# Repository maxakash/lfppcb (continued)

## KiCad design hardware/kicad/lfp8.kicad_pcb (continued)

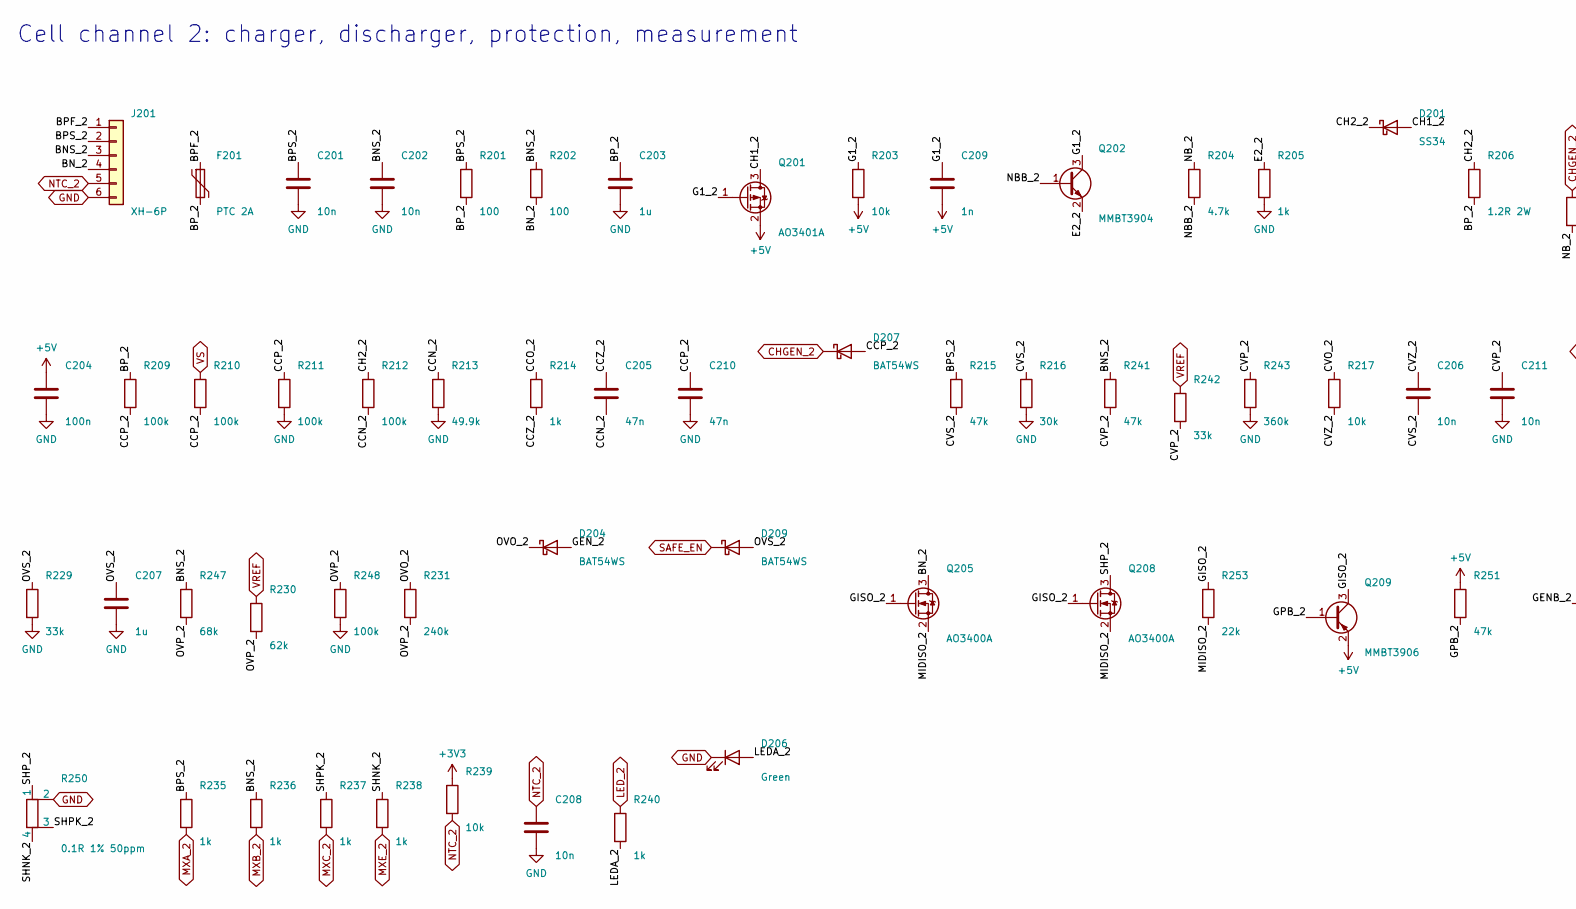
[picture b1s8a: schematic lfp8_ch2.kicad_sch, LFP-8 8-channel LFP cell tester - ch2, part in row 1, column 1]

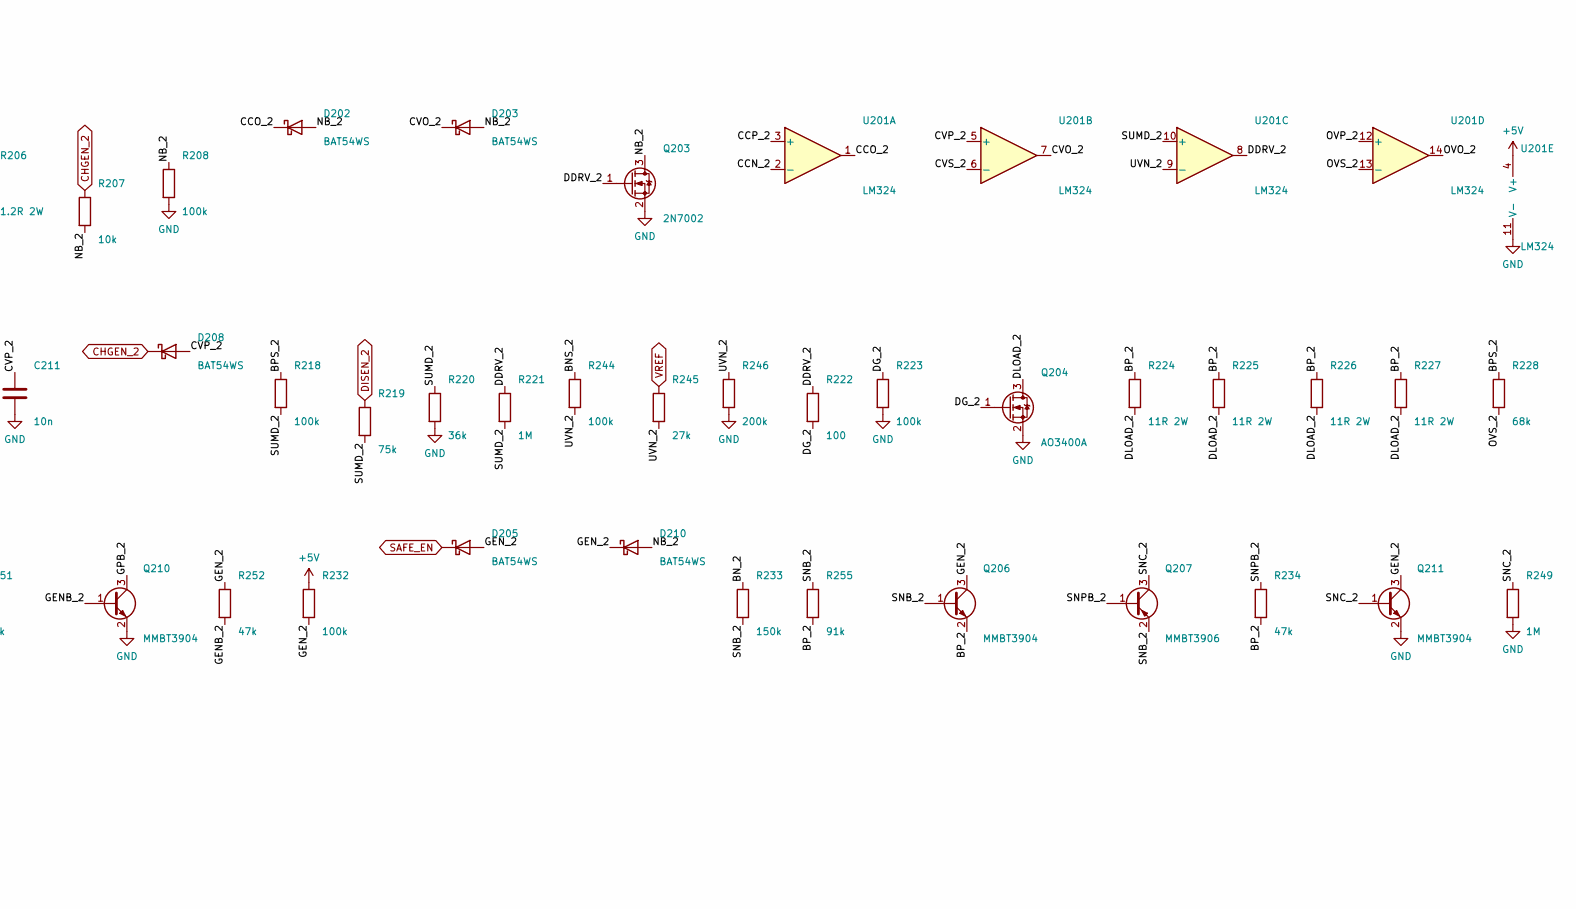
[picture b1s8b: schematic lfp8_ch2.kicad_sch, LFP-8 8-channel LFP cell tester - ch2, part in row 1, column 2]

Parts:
C201, C202, C206, C208, C211: 10n; C_0603_1608Metric; LCSC C57112
C203, C207: 1u; C_0603_1608Metric; LCSC C15849
C204: 100n; C_0603_1608Metric; LCSC C14663
C205, C210: 47n; C_0603_1608Metric; LCSC C1622
C209: 1n; C_0603_1608Metric; LCSC C1588
D201: SS34; D_SMA; MPN SS34; LCSC C8678
D202, D203, D204, D205, D207, D208, D209, D210: BAT54WS; D_SOD-323; MPN BAT54WS; LCSC C7502694
D206: Green; LED_0805_2012Metric; MPN 0805 green; LCSC C2297
F201: PTC 2A; Fuse_1812_4532Metric; MPN 1812L200/30GR; LCSC C18198342
J201: XH-6P; JST_XH_B6B-XH-A_1x06_P2.50mm_Vertical; MPN JST B6B-XH-A (or clone); JLC Hand
Q201: AO3401A; SOT-23; MPN AO3401A; LCSC C15127
Q202, Q206, Q210, Q211: MMBT3904; SOT-23; MPN MMBT3904; LCSC C20526
Q203: 2N7002; SOT-23; MPN 2N7002; LCSC C8545
Q204, Q205, Q208: AO3400A; SOT-23; MPN AO3400A; LCSC C20917
Q207, Q209: MMBT3906; SOT-23; MPN MMBT3906; LCSC C7420354
R201, R202, R222: 100; R_0603_1608Metric; LCSC C22775
R203, R207, R217, R239: 10k; R_0603_1608Metric; LCSC C25804
R204: 4.7k; R_0603_1608Metric; LCSC C23162
R205, R214, R235, R236, R237, R238, R240: 1k; R_0603_1608Metric; LCSC C21190
R206: 1.2R 2W; R_2512_6332Metric; MPN FRP2512F1R20TS; LCSC C7468247
R208, R209, R210, R211, R212, R218, R223, R232, R244, R248: 100k; R_0603_1608Metric; LCSC C25803
R213: 49.9k; R_0603_1608Metric; LCSC C23184
R215, R234, R241, R251, R252: 47k; R_0603_1608Metric; LCSC C25819
R216: 30k; R_0603_1608Metric; LCSC C22984
R219: 75k; R_0603_1608Metric; LCSC C23242
R220: 36k; R_0603_1608Metric; LCSC C23147
R221, R249: 1M; R_0603_1608Metric; LCSC C22935
R224, R225, R226, R227: 11R 2W; R_2512_6332Metric; MPN FRP2512F11R0TS; LCSC C7468192
R228, R247: 68k; R_0603_1608Metric; LCSC C23231
R229, R242: 33k; R_0603_1608Metric; LCSC C4216
R230: 62k; R_0603_1608Metric; LCSC C23221
R231: 240k; R_0603_1608Metric; LCSC C4197
R233: 150k; R_0603_1608Metric; LCSC C22807
R243: 360k; R_0603_1608Metric; LCSC C23146
R245: 27k; R_0603_1608Metric; LCSC C22967
R246: 200k; R_0603_1608Metric; LCSC C25811
R250: 0.1R 1% 50ppm; R_2512_Kelvin; MPN FRM252WFR100TN; LCSC C7420048
R253: 22k; R_0603_1608Metric; LCSC C31850
R255: 91k; R_0603_1608Metric; LCSC C23265
U201: LM324; SOIC-14_3.9x8.7mm_P1.27mm; MPN LM324DT; LCSC C71035

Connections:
+3V3: R239.1; also elsewhere on the board
+5V: C204.1, C209.2, Q201.2 (S), Q209.2 (E), R203.2, R232.1, R251.1, U201.4 (V+); also elsewhere on the board
/ch2/BNS_2: C202.1, J201.3, R202.1, R236.1, R241.1, R244.1, R247.1
/ch2/BN_2: J201.4, Q205.3 (D), R202.2, R233.1
/ch2/BPF_2: F201.1, J201.1
/ch2/BPS_2: C201.1, J201.2, R201.1, R215.1, R218.1, R228.1, R235.1
/ch2/BP_2: C203.1, F201.2, Q206.2 (E), R201.2, R206.2, R209.1, R224.1, R225.1, R226.1, R227.1, R234.2, R255.2
/ch2/CCN_2: C205.2, R212.2, R213.1, U201.2 (-)
/ch2/CCO_2: D202.1 (K), R214.1, U201.1
/ch2/CCP_2: C210.1, D207.2 (A), R209.2, R210.2, R211.1, U201.3 (+)
/ch2/CCZ_2: C205.1, R214.2
/ch2/CH1_2: D201.2 (A), Q201.3 (D)
/ch2/CH2_2: D201.1 (K), R206.1, R212.1
/ch2/CVO_2: D203.1 (K), R217.1, U201.7
/ch2/CVP_2: C211.1, D208.2 (A), R241.2, R242.2, R243.1, U201.5 (+)
/ch2/CVS_2: C206.2, R215.2, R216.1, U201.6 (-)
/ch2/CVZ_2: C206.1, R217.2
/ch2/DDRV_2: Q203.1 (G), R221.1, R222.1, U201.8
/ch2/DG_2: Q204.1 (G), R222.2, R223.1
/ch2/DLOAD_2: Q204.3 (D), R224.2, R225.2, R226.2, R227.2
/ch2/E2_2: Q202.2 (E), R205.1
/ch2/G1_2: C209.1, Q201.1 (G), Q202.3 (C), R203.1
/ch2/GENB_2: Q210.1 (B), R252.2
/ch2/GEN_2: D204.2 (A), D205.2 (A), D210.1 (K), Q206.3 (C), Q211.3 (C), R232.2, R252.1
/ch2/GISO_2: Q205.1 (G), Q208.1 (G), Q209.3 (C), R253.1
/ch2/GPB_2: Q209.1 (B), Q210.3 (C), R251.2
/ch2/LEDA_2: D206.2 (A), R240.2
/ch2/MIDISO_2: Q205.2 (S), Q208.2 (S), R253.2
/ch2/NBB_2: Q202.1 (B), R204.2
/ch2/NB_2: D202.2 (A), D203.2 (A), D210.2 (A), Q203.3 (D), R204.1, R207.2, R208.1
/ch2/OVO_2: D204.1 (K), R231.1, U201.14
/ch2/OVP_2: R230.2, R231.2, R247.2, R248.1, U201.12 (+)
/ch2/OVS_2: C207.1, D209.2 (A), R228.2, R229.1, U201.13 (-)
/ch2/SHNK_2: R238.1, R250.4
/ch2/SHPK_2: R237.1, R250.3
/ch2/SHP_2: Q208.3 (D), R250.1
/ch2/SNB_2: Q206.1 (B), Q207.2 (E), R233.2, R255.1
/ch2/SNC_2: Q207.3 (C), Q211.1 (B), R249.1
/ch2/SNPB_2: Q207.1 (B), R234.1
/ch2/SUMD_2: R218.2, R219.2, R220.1, R221.2, U201.10 (+)
/ch2/UVN_2: R244.2, R245.2, R246.1, U201.9 (-)
CHGEN_2: D207.1 (K), D208.1 (K), R207.1; also elsewhere on the board
DISEN_2: R219.1; also elsewhere on the board
GND: C201.2, C202.2, C203.2, C204.2, C207.2, C208.2, C210.2, C211.2, D206.1 (K), J201.6, Q203.2 (S), Q204.2 (S), Q210.2 (E), Q211.2 (E), R205.2, R208.2, R211.2, R213.2, R216.2, R220.2, R223.2, R229.2, R243.2, R246.2, R248.2, R249.2, R250.2, U201.11 (V-); also elsewhere on the board
LED_2: R240.1; also elsewhere on the board
MXA_2: R235.2; also elsewhere on the board
MXB_2: R236.2; also elsewhere on the board
MXC_2: R237.2; also elsewhere on the board
MXE_2: R238.2; also elsewhere on the board
NTC_2: C208.1, J201.5, R239.2; also elsewhere on the board
SAFE_EN: D205.1 (K), D209.1 (K); also elsewhere on the board
VREF: R230.1, R242.1, R245.1; also elsewhere on the board
VS: R210.1; also elsewhere on the board

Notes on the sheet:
Cell channel 2: charger, discharger, protection, measurement

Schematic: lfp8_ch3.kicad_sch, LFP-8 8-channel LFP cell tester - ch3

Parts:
C301, C302, C306, C308, C311: 10n; C_0603_1608Metric; LCSC C57112
C303, C307: 1u; C_0603_1608Metric; LCSC C15849
C304: 100n; C_0603_1608Metric; LCSC C14663
C305, C310: 47n; C_0603_1608Metric; LCSC C1622
C309: 1n; C_0603_1608Metric; LCSC C1588
D301: SS34; D_SMA; MPN SS34; LCSC C8678
D302, D303, D304, D305, D307, D308, D309, D310: BAT54WS; D_SOD-323; MPN BAT54WS; LCSC C7502694
D306: Green; LED_0805_2012Metric; MPN 0805 green; LCSC C2297
F301: PTC 2A; Fuse_1812_4532Metric; MPN 1812L200/30GR; LCSC C18198342
J301: XH-6P; JST_XH_B6B-XH-A_1x06_P2.50mm_Vertical; MPN JST B6B-XH-A (or clone); JLC Hand
Q301: AO3401A; SOT-23; MPN AO3401A; LCSC C15127
Q302, Q306, Q310, Q311: MMBT3904; SOT-23; MPN MMBT3904; LCSC C20526
Q303: 2N7002; SOT-23; MPN 2N7002; LCSC C8545
Q304, Q305, Q308: AO3400A; SOT-23; MPN AO3400A; LCSC C20917
Q307, Q309: MMBT3906; SOT-23; MPN MMBT3906; LCSC C7420354
R301, R302, R322: 100; R_0603_1608Metric; LCSC C22775
R303, R307, R317, R339: 10k; R_0603_1608Metric; LCSC C25804
R304: 4.7k; R_0603_1608Metric; LCSC C23162
R305, R314, R335, R336, R337, R338, R340: 1k; R_0603_1608Metric; LCSC C21190
R306: 1.2R 2W; R_2512_6332Metric; MPN FRP2512F1R20TS; LCSC C7468247
R308, R309, R310, R311, R312, R318, R323, R332, R344, R348: 100k; R_0603_1608Metric; LCSC C25803
R313: 49.9k; R_0603_1608Metric; LCSC C23184
R315, R334, R341, R351, R352: 47k; R_0603_1608Metric; LCSC C25819
R316: 30k; R_0603_1608Metric; LCSC C22984
R319: 75k; R_0603_1608Metric; LCSC C23242
R320: 36k; R_0603_1608Metric; LCSC C23147
R321, R349: 1M; R_0603_1608Metric; LCSC C22935
R324, R325, R326, R327: 11R 2W; R_2512_6332Metric; MPN FRP2512F11R0TS; LCSC C7468192
R328, R347: 68k; R_0603_1608Metric; LCSC C23231
R329, R342: 33k; R_0603_1608Metric; LCSC C4216
R330: 62k; R_0603_1608Metric; LCSC C23221
R331: 240k; R_0603_1608Metric; LCSC C4197
R333: 150k; R_0603_1608Metric; LCSC C22807
R343: 360k; R_0603_1608Metric; LCSC C23146
R345: 27k; R_0603_1608Metric; LCSC C22967
R346: 200k; R_0603_1608Metric; LCSC C25811
R350: 0.1R 1% 50ppm; R_2512_Kelvin; MPN FRM252WFR100TN; LCSC C7420048
R353: 22k; R_0603_1608Metric; LCSC C31850
R355: 91k; R_0603_1608Metric; LCSC C23265
U301: LM324; SOIC-14_3.9x8.7mm_P1.27mm; MPN LM324DT; LCSC C71035

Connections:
+3V3: R339.1; also elsewhere on the board
+5V: C304.1, C309.2, Q301.2 (S), Q309.2 (E), R303.2, R332.1, R351.1, U301.4 (V+); also elsewhere on the board
/ch3/BNS_3: C302.1, J301.3, R302.1, R336.1, R341.1, R344.1, R347.1
/ch3/BN_3: J301.4, Q305.3 (D), R302.2, R333.1
/ch3/BPF_3: F301.1, J301.1
/ch3/BPS_3: C301.1, J301.2, R301.1, R315.1, R318.1, R328.1, R335.1
/ch3/BP_3: C303.1, F301.2, Q306.2 (E), R301.2, R306.2, R309.1, R324.1, R325.1, R326.1, R327.1, R334.2, R355.2
/ch3/CCN_3: C305.2, R312.2, R313.1, U301.2 (-)
/ch3/CCO_3: D302.1 (K), R314.1, U301.1
/ch3/CCP_3: C310.1, D307.2 (A), R309.2, R310.2, R311.1, U301.3 (+)
/ch3/CCZ_3: C305.1, R314.2
/ch3/CH1_3: D301.2 (A), Q301.3 (D)
/ch3/CH2_3: D301.1 (K), R306.1, R312.1
/ch3/CVO_3: D303.1 (K), R317.1, U301.7
/ch3/CVP_3: C311.1, D308.2 (A), R341.2, R342.2, R343.1, U301.5 (+)
/ch3/CVS_3: C306.2, R315.2, R316.1, U301.6 (-)
/ch3/CVZ_3: C306.1, R317.2
/ch3/DDRV_3: Q303.1 (G), R321.1, R322.1, U301.8
/ch3/DG_3: Q304.1 (G), R322.2, R323.1
/ch3/DLOAD_3: Q304.3 (D), R324.2, R325.2, R326.2, R327.2
/ch3/E2_3: Q302.2 (E), R305.1
/ch3/G1_3: C309.1, Q301.1 (G), Q302.3 (C), R303.1
/ch3/GENB_3: Q310.1 (B), R352.2
/ch3/GEN_3: D304.2 (A), D305.2 (A), D310.1 (K), Q306.3 (C), Q311.3 (C), R332.2, R352.1
/ch3/GISO_3: Q305.1 (G), Q308.1 (G), Q309.3 (C), R353.1
/ch3/GPB_3: Q309.1 (B), Q310.3 (C), R351.2
/ch3/LEDA_3: D306.2 (A), R340.2
/ch3/MIDISO_3: Q305.2 (S), Q308.2 (S), R353.2
/ch3/NBB_3: Q302.1 (B), R304.2
/ch3/NB_3: D302.2 (A), D303.2 (A), D310.2 (A), Q303.3 (D), R304.1, R307.2, R308.1
/ch3/OVO_3: D304.1 (K), R331.1, U301.14
/ch3/OVP_3: R330.2, R331.2, R347.2, R348.1, U301.12 (+)
/ch3/OVS_3: C307.1, D309.2 (A), R328.2, R329.1, U301.13 (-)
/ch3/SHNK_3: R338.1, R350.4
/ch3/SHPK_3: R337.1, R350.3
/ch3/SHP_3: Q308.3 (D), R350.1
/ch3/SNB_3: Q306.1 (B), Q307.2 (E), R333.2, R355.1
/ch3/SNC_3: Q307.3 (C), Q311.1 (B), R349.1
/ch3/SNPB_3: Q307.1 (B), R334.1
/ch3/SUMD_3: R318.2, R319.2, R320.1, R321.2, U301.10 (+)
/ch3/UVN_3: R344.2, R345.2, R346.1, U301.9 (-)
CHGEN_3: D307.1 (K), D308.1 (K), R307.1; also elsewhere on the board
DISEN_3: R319.1; also elsewhere on the board
GND: C301.2, C302.2, C303.2, C304.2, C307.2, C308.2, C310.2, C311.2, D306.1 (K), J301.6, Q303.2 (S), Q304.2 (S), Q310.2 (E), Q311.2 (E), R305.2, R308.2, R311.2, R313.2, R316.2, R320.2, R323.2, R329.2, R343.2, R346.2, R348.2, R349.2, R350.2, U301.11 (V-); also elsewhere on the board
LED_3: R340.1; also elsewhere on the board
MXA_3: R335.2; also elsewhere on the board
MXB_3: R336.2; also elsewhere on the board
MXC_3: R337.2; also elsewhere on the board
MXE_3: R338.2; also elsewhere on the board
NTC_3: C308.1, J301.5, R339.2; also elsewhere on the board
SAFE_EN: D305.1 (K), D309.1 (K); also elsewhere on the board
VREF: R330.1, R342.1, R345.1; also elsewhere on the board
VS: R310.1; also elsewhere on the board

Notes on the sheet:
Cell channel 3: charger, discharger, protection, measurement

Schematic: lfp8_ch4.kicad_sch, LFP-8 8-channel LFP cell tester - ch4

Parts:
C401, C402, C406, C408, C411: 10n; C_0603_1608Metric; LCSC C57112
C403, C407: 1u; C_0603_1608Metric; LCSC C15849
C404: 100n; C_0603_1608Metric; LCSC C14663
C405, C410: 47n; C_0603_1608Metric; LCSC C1622
C409: 1n; C_0603_1608Metric; LCSC C1588
D401: SS34; D_SMA; MPN SS34; LCSC C8678
D402, D403, D404, D405, D407, D408, D409, D410: BAT54WS; D_SOD-323; MPN BAT54WS; LCSC C7502694
D406: Green; LED_0805_2012Metric; MPN 0805 green; LCSC C2297
F401: PTC 2A; Fuse_1812_4532Metric; MPN 1812L200/30GR; LCSC C18198342
J401: XH-6P; JST_XH_B6B-XH-A_1x06_P2.50mm_Vertical; MPN JST B6B-XH-A (or clone); JLC Hand
Q401: AO3401A; SOT-23; MPN AO3401A; LCSC C15127
Q402, Q406, Q410, Q411: MMBT3904; SOT-23; MPN MMBT3904; LCSC C20526
Q403: 2N7002; SOT-23; MPN 2N7002; LCSC C8545
Q404, Q405, Q408: AO3400A; SOT-23; MPN AO3400A; LCSC C20917
Q407, Q409: MMBT3906; SOT-23; MPN MMBT3906; LCSC C7420354
R401, R402, R422: 100; R_0603_1608Metric; LCSC C22775
R403, R407, R417, R439: 10k; R_0603_1608Metric; LCSC C25804
R404: 4.7k; R_0603_1608Metric; LCSC C23162
R405, R414, R435, R436, R437, R438, R440: 1k; R_0603_1608Metric; LCSC C21190
R406: 1.2R 2W; R_2512_6332Metric; MPN FRP2512F1R20TS; LCSC C7468247
R408, R409, R410, R411, R412, R418, R423, R432, R444, R448: 100k; R_0603_1608Metric; LCSC C25803
R413: 49.9k; R_0603_1608Metric; LCSC C23184
R415, R434, R441, R451, R452: 47k; R_0603_1608Metric; LCSC C25819
R416: 30k; R_0603_1608Metric; LCSC C22984
R419: 75k; R_0603_1608Metric; LCSC C23242
R420: 36k; R_0603_1608Metric; LCSC C23147
R421, R449: 1M; R_0603_1608Metric; LCSC C22935
R424, R425, R426, R427: 11R 2W; R_2512_6332Metric; MPN FRP2512F11R0TS; LCSC C7468192
R428, R447: 68k; R_0603_1608Metric; LCSC C23231
R429, R442: 33k; R_0603_1608Metric; LCSC C4216
R430: 62k; R_0603_1608Metric; LCSC C23221
R431: 240k; R_0603_1608Metric; LCSC C4197
R433: 150k; R_0603_1608Metric; LCSC C22807
R443: 360k; R_0603_1608Metric; LCSC C23146
R445: 27k; R_0603_1608Metric; LCSC C22967
R446: 200k; R_0603_1608Metric; LCSC C25811
R450: 0.1R 1% 50ppm; R_2512_Kelvin; MPN FRM252WFR100TN; LCSC C7420048
R453: 22k; R_0603_1608Metric; LCSC C31850
R455: 91k; R_0603_1608Metric; LCSC C23265
U401: LM324; SOIC-14_3.9x8.7mm_P1.27mm; MPN LM324DT; LCSC C71035

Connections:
+3V3: R439.1; also elsewhere on the board
+5V: C404.1, C409.2, Q401.2 (S), Q409.2 (E), R403.2, R432.1, R451.1, U401.4 (V+); also elsewhere on the board
/ch4/BNS_4: C402.1, J401.3, R402.1, R436.1, R441.1, R444.1, R447.1
/ch4/BN_4: J401.4, Q405.3 (D), R402.2, R433.1
/ch4/BPF_4: F401.1, J401.1
/ch4/BPS_4: C401.1, J401.2, R401.1, R415.1, R418.1, R428.1, R435.1
/ch4/BP_4: C403.1, F401.2, Q406.2 (E), R401.2, R406.2, R409.1, R424.1, R425.1, R426.1, R427.1, R434.2, R455.2
/ch4/CCN_4: C405.2, R412.2, R413.1, U401.2 (-)
/ch4/CCO_4: D402.1 (K), R414.1, U401.1
/ch4/CCP_4: C410.1, D407.2 (A), R409.2, R410.2, R411.1, U401.3 (+)
/ch4/CCZ_4: C405.1, R414.2
/ch4/CH1_4: D401.2 (A), Q401.3 (D)
/ch4/CH2_4: D401.1 (K), R406.1, R412.1
/ch4/CVO_4: D403.1 (K), R417.1, U401.7
/ch4/CVP_4: C411.1, D408.2 (A), R441.2, R442.2, R443.1, U401.5 (+)
/ch4/CVS_4: C406.2, R415.2, R416.1, U401.6 (-)
/ch4/CVZ_4: C406.1, R417.2
/ch4/DDRV_4: Q403.1 (G), R421.1, R422.1, U401.8
/ch4/DG_4: Q404.1 (G), R422.2, R423.1
/ch4/DLOAD_4: Q404.3 (D), R424.2, R425.2, R426.2, R427.2
/ch4/E2_4: Q402.2 (E), R405.1
/ch4/G1_4: C409.1, Q401.1 (G), Q402.3 (C), R403.1
/ch4/GENB_4: Q410.1 (B), R452.2
/ch4/GEN_4: D404.2 (A), D405.2 (A), D410.1 (K), Q406.3 (C), Q411.3 (C), R432.2, R452.1
/ch4/GISO_4: Q405.1 (G), Q408.1 (G), Q409.3 (C), R453.1
/ch4/GPB_4: Q409.1 (B), Q410.3 (C), R451.2
/ch4/LEDA_4: D406.2 (A), R440.2
/ch4/MIDISO_4: Q405.2 (S), Q408.2 (S), R453.2
/ch4/NBB_4: Q402.1 (B), R404.2
/ch4/NB_4: D402.2 (A), D403.2 (A), D410.2 (A), Q403.3 (D), R404.1, R407.2, R408.1
/ch4/OVO_4: D404.1 (K), R431.1, U401.14
/ch4/OVP_4: R430.2, R431.2, R447.2, R448.1, U401.12 (+)
/ch4/OVS_4: C407.1, D409.2 (A), R428.2, R429.1, U401.13 (-)
/ch4/SHNK_4: R438.1, R450.4
/ch4/SHPK_4: R437.1, R450.3
/ch4/SHP_4: Q408.3 (D), R450.1
/ch4/SNB_4: Q406.1 (B), Q407.2 (E), R433.2, R455.1
/ch4/SNC_4: Q407.3 (C), Q411.1 (B), R449.1
/ch4/SNPB_4: Q407.1 (B), R434.1
/ch4/SUMD_4: R418.2, R419.2, R420.1, R421.2, U401.10 (+)
/ch4/UVN_4: R444.2, R445.2, R446.1, U401.9 (-)
CHGEN_4: D407.1 (K), D408.1 (K), R407.1; also elsewhere on the board
DISEN_4: R419.1; also elsewhere on the board
GND: C401.2, C402.2, C403.2, C404.2, C407.2, C408.2, C410.2, C411.2, D406.1 (K), J401.6, Q403.2 (S), Q404.2 (S), Q410.2 (E), Q411.2 (E), R405.2, R408.2, R411.2, R413.2, R416.2, R420.2, R423.2, R429.2, R443.2, R446.2, R448.2, R449.2, R450.2, U401.11 (V-); also elsewhere on the board
LED_4: R440.1; also elsewhere on the board
MXA_4: R435.2; also elsewhere on the board
MXB_4: R436.2; also elsewhere on the board
MXC_4: R437.2; also elsewhere on the board
MXE_4: R438.2; also elsewhere on the board
NTC_4: C408.1, J401.5, R439.2; also elsewhere on the board
SAFE_EN: D405.1 (K), D409.1 (K); also elsewhere on the board
VREF: R430.1, R442.1, R445.1; also elsewhere on the board
VS: R410.1; also elsewhere on the board

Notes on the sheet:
Cell channel 4: charger, discharger, protection, measurement

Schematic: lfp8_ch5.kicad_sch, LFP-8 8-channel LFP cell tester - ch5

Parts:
C501, C502, C506, C508, C511: 10n; C_0603_1608Metric; LCSC C57112
C503, C507: 1u; C_0603_1608Metric; LCSC C15849
C504: 100n; C_0603_1608Metric; LCSC C14663
C505, C510: 47n; C_0603_1608Metric; LCSC C1622
C509: 1n; C_0603_1608Metric; LCSC C1588
D501: SS34; D_SMA; MPN SS34; LCSC C8678
D502, D503, D504, D505, D507, D508, D509, D510: BAT54WS; D_SOD-323; MPN BAT54WS; LCSC C7502694
D506: Green; LED_0805_2012Metric; MPN 0805 green; LCSC C2297
F501: PTC 2A; Fuse_1812_4532Metric; MPN 1812L200/30GR; LCSC C18198342
J501: XH-6P; JST_XH_B6B-XH-A_1x06_P2.50mm_Vertical; MPN JST B6B-XH-A (or clone); JLC Hand
Q501: AO3401A; SOT-23; MPN AO3401A; LCSC C15127
Q502, Q506, Q510, Q511: MMBT3904; SOT-23; MPN MMBT3904; LCSC C20526
Q503: 2N7002; SOT-23; MPN 2N7002; LCSC C8545
Q504, Q505, Q508: AO3400A; SOT-23; MPN AO3400A; LCSC C20917
Q507, Q509: MMBT3906; SOT-23; MPN MMBT3906; LCSC C7420354
R501, R502, R522: 100; R_0603_1608Metric; LCSC C22775
R503, R507, R517, R539: 10k; R_0603_1608Metric; LCSC C25804
R504: 4.7k; R_0603_1608Metric; LCSC C23162
R505, R514, R535, R536, R537, R538, R540: 1k; R_0603_1608Metric; LCSC C21190
R506: 1.2R 2W; R_2512_6332Metric; MPN FRP2512F1R20TS; LCSC C7468247
R508, R509, R510, R511, R512, R518, R523, R532, R544, R548: 100k; R_0603_1608Metric; LCSC C25803
R513: 49.9k; R_0603_1608Metric; LCSC C23184
R515, R534, R541, R551, R552: 47k; R_0603_1608Metric; LCSC C25819
R516: 30k; R_0603_1608Metric; LCSC C22984
R519: 75k; R_0603_1608Metric; LCSC C23242
R520: 36k; R_0603_1608Metric; LCSC C23147
R521, R549: 1M; R_0603_1608Metric; LCSC C22935
R524, R525, R526, R527: 11R 2W; R_2512_6332Metric; MPN FRP2512F11R0TS; LCSC C7468192
R528, R547: 68k; R_0603_1608Metric; LCSC C23231
R529, R542: 33k; R_0603_1608Metric; LCSC C4216
R530: 62k; R_0603_1608Metric; LCSC C23221
R531: 240k; R_0603_1608Metric; LCSC C4197
R533: 150k; R_0603_1608Metric; LCSC C22807
R543: 360k; R_0603_1608Metric; LCSC C23146
R545: 27k; R_0603_1608Metric; LCSC C22967
R546: 200k; R_0603_1608Metric; LCSC C25811
R550: 0.1R 1% 50ppm; R_2512_Kelvin; MPN FRM252WFR100TN; LCSC C7420048
R553: 22k; R_0603_1608Metric; LCSC C31850
R555: 91k; R_0603_1608Metric; LCSC C23265
U501: LM324; SOIC-14_3.9x8.7mm_P1.27mm; MPN LM324DT; LCSC C71035

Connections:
+3V3: R539.1; also elsewhere on the board
+5V: C504.1, C509.2, Q501.2 (S), Q509.2 (E), R503.2, R532.1, R551.1, U501.4 (V+); also elsewhere on the board
/ch5/BNS_5: C502.1, J501.3, R502.1, R536.1, R541.1, R544.1, R547.1
/ch5/BN_5: J501.4, Q505.3 (D), R502.2, R533.1
/ch5/BPF_5: F501.1, J501.1
/ch5/BPS_5: C501.1, J501.2, R501.1, R515.1, R518.1, R528.1, R535.1
/ch5/BP_5: C503.1, F501.2, Q506.2 (E), R501.2, R506.2, R509.1, R524.1, R525.1, R526.1, R527.1, R534.2, R555.2
/ch5/CCN_5: C505.2, R512.2, R513.1, U501.2 (-)
/ch5/CCO_5: D502.1 (K), R514.1, U501.1
/ch5/CCP_5: C510.1, D507.2 (A), R509.2, R510.2, R511.1, U501.3 (+)
/ch5/CCZ_5: C505.1, R514.2
/ch5/CH1_5: D501.2 (A), Q501.3 (D)
/ch5/CH2_5: D501.1 (K), R506.1, R512.1
/ch5/CVO_5: D503.1 (K), R517.1, U501.7
/ch5/CVP_5: C511.1, D508.2 (A), R541.2, R542.2, R543.1, U501.5 (+)
/ch5/CVS_5: C506.2, R515.2, R516.1, U501.6 (-)
/ch5/CVZ_5: C506.1, R517.2
/ch5/DDRV_5: Q503.1 (G), R521.1, R522.1, U501.8
/ch5/DG_5: Q504.1 (G), R522.2, R523.1
/ch5/DLOAD_5: Q504.3 (D), R524.2, R525.2, R526.2, R527.2
/ch5/E2_5: Q502.2 (E), R505.1
/ch5/G1_5: C509.1, Q501.1 (G), Q502.3 (C), R503.1
/ch5/GENB_5: Q510.1 (B), R552.2
/ch5/GEN_5: D504.2 (A), D505.2 (A), D510.1 (K), Q506.3 (C), Q511.3 (C), R532.2, R552.1
/ch5/GISO_5: Q505.1 (G), Q508.1 (G), Q509.3 (C), R553.1
/ch5/GPB_5: Q509.1 (B), Q510.3 (C), R551.2
/ch5/LEDA_5: D506.2 (A), R540.2
/ch5/MIDISO_5: Q505.2 (S), Q508.2 (S), R553.2
/ch5/NBB_5: Q502.1 (B), R504.2
/ch5/NB_5: D502.2 (A), D503.2 (A), D510.2 (A), Q503.3 (D), R504.1, R507.2, R508.1
/ch5/OVO_5: D504.1 (K), R531.1, U501.14
/ch5/OVP_5: R530.2, R531.2, R547.2, R548.1, U501.12 (+)
/ch5/OVS_5: C507.1, D509.2 (A), R528.2, R529.1, U501.13 (-)
/ch5/SHNK_5: R538.1, R550.4
/ch5/SHPK_5: R537.1, R550.3
/ch5/SHP_5: Q508.3 (D), R550.1
/ch5/SNB_5: Q506.1 (B), Q507.2 (E), R533.2, R555.1
/ch5/SNC_5: Q507.3 (C), Q511.1 (B), R549.1
/ch5/SNPB_5: Q507.1 (B), R534.1
/ch5/SUMD_5: R518.2, R519.2, R520.1, R521.2, U501.10 (+)
/ch5/UVN_5: R544.2, R545.2, R546.1, U501.9 (-)
CHGEN_5: D507.1 (K), D508.1 (K), R507.1; also elsewhere on the board
DISEN_5: R519.1; also elsewhere on the board
GND: C501.2, C502.2, C503.2, C504.2, C507.2, C508.2, C510.2, C511.2, D506.1 (K), J501.6, Q503.2 (S), Q504.2 (S), Q510.2 (E), Q511.2 (E), R505.2, R508.2, R511.2, R513.2, R516.2, R520.2, R523.2, R529.2, R543.2, R546.2, R548.2, R549.2, R550.2, U501.11 (V-); also elsewhere on the board
LED_5: R540.1; also elsewhere on the board
MXA_5: R535.2; also elsewhere on the board
MXB_5: R536.2; also elsewhere on the board
MXC_5: R537.2; also elsewhere on the board
MXE_5: R538.2; also elsewhere on the board
NTC_5: C508.1, J501.5, R539.2; also elsewhere on the board
SAFE_EN: D505.1 (K), D509.1 (K); also elsewhere on the board
VREF: R530.1, R542.1, R545.1; also elsewhere on the board
VS: R510.1; also elsewhere on the board

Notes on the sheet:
Cell channel 5: charger, discharger, protection, measurement

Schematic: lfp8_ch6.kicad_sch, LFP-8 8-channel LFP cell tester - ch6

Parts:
C601, C602, C606, C608, C611: 10n; C_0603_1608Metric; LCSC C57112
C603, C607: 1u; C_0603_1608Metric; LCSC C15849
C604: 100n; C_0603_1608Metric; LCSC C14663
C605, C610: 47n; C_0603_1608Metric; LCSC C1622
C609: 1n; C_0603_1608Metric; LCSC C1588
D601: SS34; D_SMA; MPN SS34; LCSC C8678
D602, D603, D604, D605, D607, D608, D609, D610: BAT54WS; D_SOD-323; MPN BAT54WS; LCSC C7502694
D606: Green; LED_0805_2012Metric; MPN 0805 green; LCSC C2297
F601: PTC 2A; Fuse_1812_4532Metric; MPN 1812L200/30GR; LCSC C18198342
J601: XH-6P; JST_XH_B6B-XH-A_1x06_P2.50mm_Vertical; MPN JST B6B-XH-A (or clone); JLC Hand
Q601: AO3401A; SOT-23; MPN AO3401A; LCSC C15127
Q602, Q606, Q610, Q611: MMBT3904; SOT-23; MPN MMBT3904; LCSC C20526
Q603: 2N7002; SOT-23; MPN 2N7002; LCSC C8545
Q604, Q605, Q608: AO3400A; SOT-23; MPN AO3400A; LCSC C20917
Q607, Q609: MMBT3906; SOT-23; MPN MMBT3906; LCSC C7420354
R601, R602, R622: 100; R_0603_1608Metric; LCSC C22775
R603, R607, R617, R639: 10k; R_0603_1608Metric; LCSC C25804
R604: 4.7k; R_0603_1608Metric; LCSC C23162
R605, R614, R635, R636, R637, R638, R640: 1k; R_0603_1608Metric; LCSC C21190
R606: 1.2R 2W; R_2512_6332Metric; MPN FRP2512F1R20TS; LCSC C7468247
R608, R609, R610, R611, R612, R618, R623, R632, R644, R648: 100k; R_0603_1608Metric; LCSC C25803
R613: 49.9k; R_0603_1608Metric; LCSC C23184
R615, R634, R641, R651, R652: 47k; R_0603_1608Metric; LCSC C25819
R616: 30k; R_0603_1608Metric; LCSC C22984
R619: 75k; R_0603_1608Metric; LCSC C23242
R620: 36k; R_0603_1608Metric; LCSC C23147
R621, R649: 1M; R_0603_1608Metric; LCSC C22935
R624, R625, R626, R627: 11R 2W; R_2512_6332Metric; MPN FRP2512F11R0TS; LCSC C7468192
R628, R647: 68k; R_0603_1608Metric; LCSC C23231
R629, R642: 33k; R_0603_1608Metric; LCSC C4216
R630: 62k; R_0603_1608Metric; LCSC C23221
R631: 240k; R_0603_1608Metric; LCSC C4197
R633: 150k; R_0603_1608Metric; LCSC C22807
R643: 360k; R_0603_1608Metric; LCSC C23146
R645: 27k; R_0603_1608Metric; LCSC C22967
R646: 200k; R_0603_1608Metric; LCSC C25811
R650: 0.1R 1% 50ppm; R_2512_Kelvin; MPN FRM252WFR100TN; LCSC C7420048
R653: 22k; R_0603_1608Metric; LCSC C31850
R655: 91k; R_0603_1608Metric; LCSC C23265
U601: LM324; SOIC-14_3.9x8.7mm_P1.27mm; MPN LM324DT; LCSC C71035

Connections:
+3V3: R639.1; also elsewhere on the board
+5V: C604.1, C609.2, Q601.2 (S), Q609.2 (E), R603.2, R632.1, R651.1, U601.4 (V+); also elsewhere on the board
/ch6/BNS_6: C602.1, J601.3, R602.1, R636.1, R641.1, R644.1, R647.1
/ch6/BN_6: J601.4, Q605.3 (D), R602.2, R633.1
/ch6/BPF_6: F601.1, J601.1
/ch6/BPS_6: C601.1, J601.2, R601.1, R615.1, R618.1, R628.1, R635.1
/ch6/BP_6: C603.1, F601.2, Q606.2 (E), R601.2, R606.2, R609.1, R624.1, R625.1, R626.1, R627.1, R634.2, R655.2
/ch6/CCN_6: C605.2, R612.2, R613.1, U601.2 (-)
/ch6/CCO_6: D602.1 (K), R614.1, U601.1
/ch6/CCP_6: C610.1, D607.2 (A), R609.2, R610.2, R611.1, U601.3 (+)
/ch6/CCZ_6: C605.1, R614.2
/ch6/CH1_6: D601.2 (A), Q601.3 (D)
/ch6/CH2_6: D601.1 (K), R606.1, R612.1
/ch6/CVO_6: D603.1 (K), R617.1, U601.7
/ch6/CVP_6: C611.1, D608.2 (A), R641.2, R642.2, R643.1, U601.5 (+)
/ch6/CVS_6: C606.2, R615.2, R616.1, U601.6 (-)
/ch6/CVZ_6: C606.1, R617.2
/ch6/DDRV_6: Q603.1 (G), R621.1, R622.1, U601.8
/ch6/DG_6: Q604.1 (G), R622.2, R623.1
/ch6/DLOAD_6: Q604.3 (D), R624.2, R625.2, R626.2, R627.2
/ch6/E2_6: Q602.2 (E), R605.1
/ch6/G1_6: C609.1, Q601.1 (G), Q602.3 (C), R603.1
/ch6/GENB_6: Q610.1 (B), R652.2
/ch6/GEN_6: D604.2 (A), D605.2 (A), D610.1 (K), Q606.3 (C), Q611.3 (C), R632.2, R652.1
/ch6/GISO_6: Q605.1 (G), Q608.1 (G), Q609.3 (C), R653.1
/ch6/GPB_6: Q609.1 (B), Q610.3 (C), R651.2
/ch6/LEDA_6: D606.2 (A), R640.2
/ch6/MIDISO_6: Q605.2 (S), Q608.2 (S), R653.2
/ch6/NBB_6: Q602.1 (B), R604.2
/ch6/NB_6: D602.2 (A), D603.2 (A), D610.2 (A), Q603.3 (D), R604.1, R607.2, R608.1
/ch6/OVO_6: D604.1 (K), R631.1, U601.14
/ch6/OVP_6: R630.2, R631.2, R647.2, R648.1, U601.12 (+)
/ch6/OVS_6: C607.1, D609.2 (A), R628.2, R629.1, U601.13 (-)
/ch6/SHNK_6: R638.1, R650.4
/ch6/SHPK_6: R637.1, R650.3
/ch6/SHP_6: Q608.3 (D), R650.1
/ch6/SNB_6: Q606.1 (B), Q607.2 (E), R633.2, R655.1
/ch6/SNC_6: Q607.3 (C), Q611.1 (B), R649.1
/ch6/SNPB_6: Q607.1 (B), R634.1
/ch6/SUMD_6: R618.2, R619.2, R620.1, R621.2, U601.10 (+)
/ch6/UVN_6: R644.2, R645.2, R646.1, U601.9 (-)
CHGEN_6: D607.1 (K), D608.1 (K), R607.1; also elsewhere on the board
DISEN_6: R619.1; also elsewhere on the board
GND: C601.2, C602.2, C603.2, C604.2, C607.2, C608.2, C610.2, C611.2, D606.1 (K), J601.6, Q603.2 (S), Q604.2 (S), Q610.2 (E), Q611.2 (E), R605.2, R608.2, R611.2, R613.2, R616.2, R620.2, R623.2, R629.2, R643.2, R646.2, R648.2, R649.2, R650.2, U601.11 (V-); also elsewhere on the board
LED_6: R640.1; also elsewhere on the board
MXA_6: R635.2; also elsewhere on the board
MXB_6: R636.2; also elsewhere on the board
MXC_6: R637.2; also elsewhere on the board
MXE_6: R638.2; also elsewhere on the board
NTC_6: C608.1, J601.5, R639.2; also elsewhere on the board
SAFE_EN: D605.1 (K), D609.1 (K); also elsewhere on the board
VREF: R630.1, R642.1, R645.1; also elsewhere on the board
VS: R610.1; also elsewhere on the board

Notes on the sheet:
Cell channel 6: charger, discharger, protection, measurement

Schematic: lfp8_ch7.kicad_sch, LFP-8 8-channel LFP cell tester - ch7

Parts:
C701, C702, C706, C708, C711: 10n; C_0603_1608Metric; LCSC C57112
C703, C707: 1u; C_0603_1608Metric; LCSC C15849
C704: 100n; C_0603_1608Metric; LCSC C14663
C705, C710: 47n; C_0603_1608Metric; LCSC C1622
C709: 1n; C_0603_1608Metric; LCSC C1588
D701: SS34; D_SMA; MPN SS34; LCSC C8678
D702, D703, D704, D705, D707, D708, D709, D710: BAT54WS; D_SOD-323; MPN BAT54WS; LCSC C7502694
D706: Green; LED_0805_2012Metric; MPN 0805 green; LCSC C2297
F701: PTC 2A; Fuse_1812_4532Metric; MPN 1812L200/30GR; LCSC C18198342
J701: XH-6P; JST_XH_B6B-XH-A_1x06_P2.50mm_Vertical; MPN JST B6B-XH-A (or clone); JLC Hand
Q701: AO3401A; SOT-23; MPN AO3401A; LCSC C15127
Q702, Q706, Q710, Q711: MMBT3904; SOT-23; MPN MMBT3904; LCSC C20526
Q703: 2N7002; SOT-23; MPN 2N7002; LCSC C8545
Q704, Q705, Q708: AO3400A; SOT-23; MPN AO3400A; LCSC C20917
Q707, Q709: MMBT3906; SOT-23; MPN MMBT3906; LCSC C7420354
R701, R702, R722: 100; R_0603_1608Metric; LCSC C22775
R703, R707, R717, R739: 10k; R_0603_1608Metric; LCSC C25804
R704: 4.7k; R_0603_1608Metric; LCSC C23162
R705, R714, R735, R736, R737, R738, R740: 1k; R_0603_1608Metric; LCSC C21190
R706: 1.2R 2W; R_2512_6332Metric; MPN FRP2512F1R20TS; LCSC C7468247
R708, R709, R710, R711, R712, R718, R723, R732, R744, R748: 100k; R_0603_1608Metric; LCSC C25803
R713: 49.9k; R_0603_1608Metric; LCSC C23184
R715, R734, R741, R751, R752: 47k; R_0603_1608Metric; LCSC C25819
R716: 30k; R_0603_1608Metric; LCSC C22984
R719: 75k; R_0603_1608Metric; LCSC C23242
R720: 36k; R_0603_1608Metric; LCSC C23147
R721, R749: 1M; R_0603_1608Metric; LCSC C22935
R724, R725, R726, R727: 11R 2W; R_2512_6332Metric; MPN FRP2512F11R0TS; LCSC C7468192
R728, R747: 68k; R_0603_1608Metric; LCSC C23231
R729, R742: 33k; R_0603_1608Metric; LCSC C4216
R730: 62k; R_0603_1608Metric; LCSC C23221
R731: 240k; R_0603_1608Metric; LCSC C4197
R733: 150k; R_0603_1608Metric; LCSC C22807
R743: 360k; R_0603_1608Metric; LCSC C23146
R745: 27k; R_0603_1608Metric; LCSC C22967
R746: 200k; R_0603_1608Metric; LCSC C25811
R750: 0.1R 1% 50ppm; R_2512_Kelvin; MPN FRM252WFR100TN; LCSC C7420048
R753: 22k; R_0603_1608Metric; LCSC C31850
R755: 91k; R_0603_1608Metric; LCSC C23265
U701: LM324; SOIC-14_3.9x8.7mm_P1.27mm; MPN LM324DT; LCSC C71035

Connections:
+3V3: R739.1; also elsewhere on the board
+5V: C704.1, C709.2, Q701.2 (S), Q709.2 (E), R703.2, R732.1, R751.1, U701.4 (V+); also elsewhere on the board
/ch7/BNS_7: C702.1, J701.3, R702.1, R736.1, R741.1, R744.1, R747.1
/ch7/BN_7: J701.4, Q705.3 (D), R702.2, R733.1
/ch7/BPF_7: F701.1, J701.1
/ch7/BPS_7: C701.1, J701.2, R701.1, R715.1, R718.1, R728.1, R735.1
/ch7/BP_7: C703.1, F701.2, Q706.2 (E), R701.2, R706.2, R709.1, R724.1, R725.1, R726.1, R727.1, R734.2, R755.2
/ch7/CCN_7: C705.2, R712.2, R713.1, U701.2 (-)
/ch7/CCO_7: D702.1 (K), R714.1, U701.1
/ch7/CCP_7: C710.1, D707.2 (A), R709.2, R710.2, R711.1, U701.3 (+)
/ch7/CCZ_7: C705.1, R714.2
/ch7/CH1_7: D701.2 (A), Q701.3 (D)
/ch7/CH2_7: D701.1 (K), R706.1, R712.1
/ch7/CVO_7: D703.1 (K), R717.1, U701.7
/ch7/CVP_7: C711.1, D708.2 (A), R741.2, R742.2, R743.1, U701.5 (+)
/ch7/CVS_7: C706.2, R715.2, R716.1, U701.6 (-)
/ch7/CVZ_7: C706.1, R717.2
/ch7/DDRV_7: Q703.1 (G), R721.1, R722.1, U701.8
/ch7/DG_7: Q704.1 (G), R722.2, R723.1
/ch7/DLOAD_7: Q704.3 (D), R724.2, R725.2, R726.2, R727.2
/ch7/E2_7: Q702.2 (E), R705.1
/ch7/G1_7: C709.1, Q701.1 (G), Q702.3 (C), R703.1
/ch7/GENB_7: Q710.1 (B), R752.2
/ch7/GEN_7: D704.2 (A), D705.2 (A), D710.1 (K), Q706.3 (C), Q711.3 (C), R732.2, R752.1
/ch7/GISO_7: Q705.1 (G), Q708.1 (G), Q709.3 (C), R753.1
/ch7/GPB_7: Q709.1 (B), Q710.3 (C), R751.2
/ch7/LEDA_7: D706.2 (A), R740.2
/ch7/MIDISO_7: Q705.2 (S), Q708.2 (S), R753.2
/ch7/NBB_7: Q702.1 (B), R704.2
/ch7/NB_7: D702.2 (A), D703.2 (A), D710.2 (A), Q703.3 (D), R704.1, R707.2, R708.1
/ch7/OVO_7: D704.1 (K), R731.1, U701.14
/ch7/OVP_7: R730.2, R731.2, R747.2, R748.1, U701.12 (+)
/ch7/OVS_7: C707.1, D709.2 (A), R728.2, R729.1, U701.13 (-)
/ch7/SHNK_7: R738.1, R750.4
/ch7/SHPK_7: R737.1, R750.3
/ch7/SHP_7: Q708.3 (D), R750.1
/ch7/SNB_7: Q706.1 (B), Q707.2 (E), R733.2, R755.1
/ch7/SNC_7: Q707.3 (C), Q711.1 (B), R749.1
/ch7/SNPB_7: Q707.1 (B), R734.1
/ch7/SUMD_7: R718.2, R719.2, R720.1, R721.2, U701.10 (+)
/ch7/UVN_7: R744.2, R745.2, R746.1, U701.9 (-)
CHGEN_7: D707.1 (K), D708.1 (K), R707.1; also elsewhere on the board
DISEN_7: R719.1; also elsewhere on the board
GND: C701.2, C702.2, C703.2, C704.2, C707.2, C708.2, C710.2, C711.2, D706.1 (K), J701.6, Q703.2 (S), Q704.2 (S), Q710.2 (E), Q711.2 (E), R705.2, R708.2, R711.2, R713.2, R716.2, R720.2, R723.2, R729.2, R743.2, R746.2, R748.2, R749.2, R750.2, U701.11 (V-); also elsewhere on the board
LED_7: R740.1; also elsewhere on the board
MXA_7: R735.2; also elsewhere on the board
MXB_7: R736.2; also elsewhere on the board
MXC_7: R737.2; also elsewhere on the board
MXE_7: R738.2; also elsewhere on the board
NTC_7: C708.1, J701.5, R739.2; also elsewhere on the board
SAFE_EN: D705.1 (K), D709.1 (K); also elsewhere on the board
VREF: R730.1, R742.1, R745.1; also elsewhere on the board
VS: R710.1; also elsewhere on the board

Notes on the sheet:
Cell channel 7: charger, discharger, protection, measurement
